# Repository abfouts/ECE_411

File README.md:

# ECE_411 :: T08 
Group Practicum Project

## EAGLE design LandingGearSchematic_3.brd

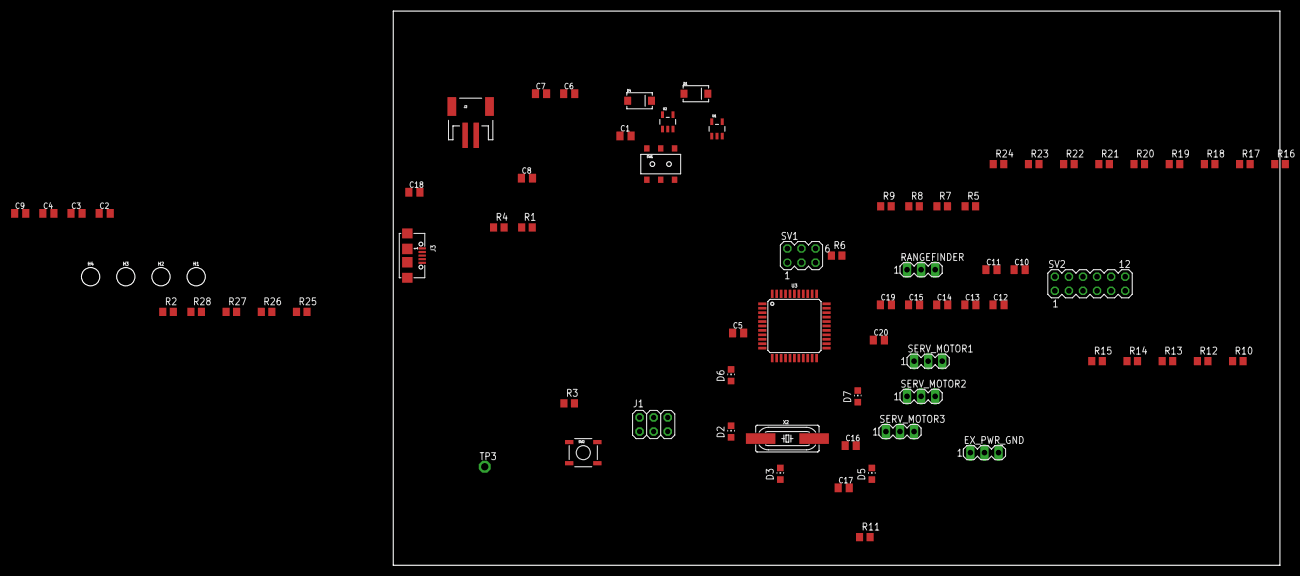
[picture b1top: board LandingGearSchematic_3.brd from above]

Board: 2 copper layers, 160.0 x 100.0 mm, 76 parts (0 on the bottom side), 69 nets, no tracks yet.

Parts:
C1: 470p; C0805K
C2, C3, C4, C9, C10, C11, C18: 100n; C0805K
C5: 1u; C0805K
C6, C7, C8, C19: 4.7u; C0805K
C12, C13, C14, C15, C20: 0.1u; C0805K
C16, C17: 30p; C0805K
D1, D4: B340A; SMA-DIODE
D2, D3, D5, D6, D7: GREEN; CHIP-LED0805
EX_PWR_GND: MA03-1
H1, H2, H3, H4: STAND-OFF
J1: 3x2 M; 2X03
J2: S2B-PH-SM4-TB(LF)(SN); JST-2-SMD
J3: 629105136821
R1, R8, R10, R11, R12: 1K; R0805
R2, R3, R6: 10K; R0805
R4, R5: 22; R0805
R7, R9, R13, R14, R15, R16, R17, R18, R19, R20, R21, R22, R23, R24, R25, R26, R27, R28: 0; R0805
RANGEFINDER: MA03-1
SERV_MOTOR1, SERV_MOTOR2, SERV_MOTOR3: MA03-1
SV1: MA03-2
SV2: MA06-2
SW1: AYZ0202AGRLC; AYZ0202
SW2: !RESET; TACTILE_SWITCH_SMD
TP3: TPPAD1-13; P1-13
U1: MCP73831; SOT23-5
U2: MIC5219; SOT23-5
U3: ATMEGA32U4-AUR; TQFP44
X2: 16 MHz; HC49UP

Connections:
3.3V: C2.1, C3.1, C8.1, C9.1, C10.1, C11.1, J1.2, R3.2, R8.2, R10.2, R12.2, U2.5, U3.14, U3.24, U3.34, U3.44
!RESET: J1.5, R3.1, SW2.3, TP3.TP, U3.13
AREF: C4.1, U3.42
D13#/USER_LED: R11.2, U3.32
D14/MISO: J1.1, U3.11
D15/SCK: J1.3, U3.9
D16/MOSI: J1.4, U3.10
D17/RX-LED: D6.C, U3.8
D+: R5.2, U3.4
D-: R4.2, U3.3
GND: C1.2, C2.2, C3.2, C4.2, C5.2, C6.2, C7.2, C8.2, C9.2, C10.2, C11.2, C12.2, C13.2, C14.2, C15.2, C16.2, C17.2, C18.2, C19.2, C20.2, D2.C, D3.C, EX_PWR_GND.1, EX_PWR_GND.3, J1.6, J2.1, J3.5, R2.1, R6.1, R7.2, R17.1, R23.2, RANGEFINDER.2, SERV_MOTOR1.3, SERV_MOTOR2.3, SERV_MOTOR3.3, SW1.3, SW2.1, U1.2, U2.2, U3.5, U3.15, U3.23, U3.35, U3.43
MCPPROG: R2.2, U1.5
MIC-BP: C1.1, U2.4
MIC-EN: SW1.2, U2.3
unnamed: R7.1, SV2.12
unnamed: D5.A, R1.1
unnamed: D5.C, U1.1
unnamed: D2.A, R10.1
unnamed: R17.2, SV2.11
unnamed: D3.A, R11.1
unnamed: C18.1, J3.SHELL, J3.SHELL1, J3.SHELL2, J3.SHELL3
unnamed: D6.A, R8.1
unnamed: D7.A, R12.1
unnamed: J3.2, R4.1
unnamed: J3.3, R5.1
unnamed: R23.1, SV1.6
NC_A0: R28.1, U3.36
NC_A0_R: R28.2, SV1.1
NC_A1: R25.2, U3.37
NC_A1_R: R25.1, SV1.2
NC_A2: R27.1, U3.38
NC_A2_R: R27.2, SV1.3
NC_A3: R24.2, U3.39
NC_A3_R: R24.1, SV1.4
NC_A4: R26.1, U3.40
NC_A4_R: R26.2, SV1.5
NC_D0: R22.1, U3.20
NC_D0_R: R22.2, SV2.1
NC_D1: R16.2, U3.21
NC_D1_R: R16.1, SV2.2
NC_D2: R21.1, U3.19
NC_D2_R: R21.2, SV2.3
NC_D3: R15.2, U3.18
NC_D3_R: R15.1, SV2.4
NC_D4: R20.1, U3.25
NC_D4_R: R20.2, SV2.5
NC_D5: R14.2, U3.31
NC_D6: R19.1, U3.27
NC_D6_R: R19.2, SV2.7
NC_D7: R13.2, U3.1
NC_D7_R: R13.1, SV2.8
NC_D11: R18.1, U3.12
NC_D11_R: R18.2, SV2.9
NC_D12: R9.2, U3.26
NC_D12_R: R9.1, SV2.10
ND_D5_R: R14.1, SV2.6
PE2/!HWB: R6.2, U3.33
PWRIN: C7.1, D1.C, D4.C, SW1.1, U2.1
RANGE_OUT: RANGEFINDER.1, U3.41
SERV1: SERV_MOTOR1.1, U3.28
SERV2: SERV_MOTOR2.1, U3.29
SERV3: SERV_MOTOR3.1, U3.30
TX_LED: D7.C, U3.22
UCAP: C5.1, U3.6
VBUS: C19.1, D4.A, J3.1, R1.2, U1.4, U3.2, U3.7
VCC: C12.1, C13.1, C14.1, C15.1, C20.1, EX_PWR_GND.2, RANGEFINDER.3, SERV_MOTOR1.2, SERV_MOTOR2.2, SERV_MOTOR3.2
V_BATT: C6.1, D1.A, J2.2, U1.3
XTAL1: C17.1, U3.17, X2.2
XTAL2: C16.1, U3.16, X2.1

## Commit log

2019-10-23 Add files via upload
    Initial buildout of BoM
2019-10-23 Delete Airplane_BlockD.jpg
    Wrong Branch
2019-10-23 Delete Project_Ideas.pdf
    Wrong Branch
2019-10-23 Delete ECE 411 BoM.xlsx
    Wrong Branch
2019-10-24 Add files via upload
    Initial PDS Launch
2019-10-24 Add files via upload
    Brief description of servo motor including which pinout for adafruit
2019-10-31 Create Schematics
2019-11-14 Add files via upload
    Latest renamed Eagle schematics
2019-11-15 REV 2
2019-11-19 REV 3
2019-11-19 REV 4
    Update: 11PM 11/18/19
    Needs ground plain and ground connections through vias
    DRC Checking needs to be done
2019-11-20 REV 5
    Needs aligned mounting holes
    Silk screen for power and GND pins
    Silk screen for our team name, board name etc in the bottom left
2019-12-02 Add files via upload
    Moved everything to MASTER branch
2019-12-04 Code for the landing gear
    WORKING for the leonardo board
2019-12-07 Final Code
2019-12-07 Board Files
2019-12-07 test
2019-12-09 Rearranged the github and placed everything in files
    Final Board Revision is #6 in brd
    Homeworks are placed in Documentation
    Arduino code in code file

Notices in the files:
parts and their libraries:
SparkFun-DiscreteSemi: Licensing: CC v3.0 Share-Alike You are welcome to use this library for commercial purposes.
SparkFun-Hardware: Licensing: Creative Commons ShareAlike 4.0 International - https://creativecommons.org/licenses/by-sa/4.0
